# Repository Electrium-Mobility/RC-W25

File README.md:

# RC-W25
Electrium Mobility W25 Remote Control Project

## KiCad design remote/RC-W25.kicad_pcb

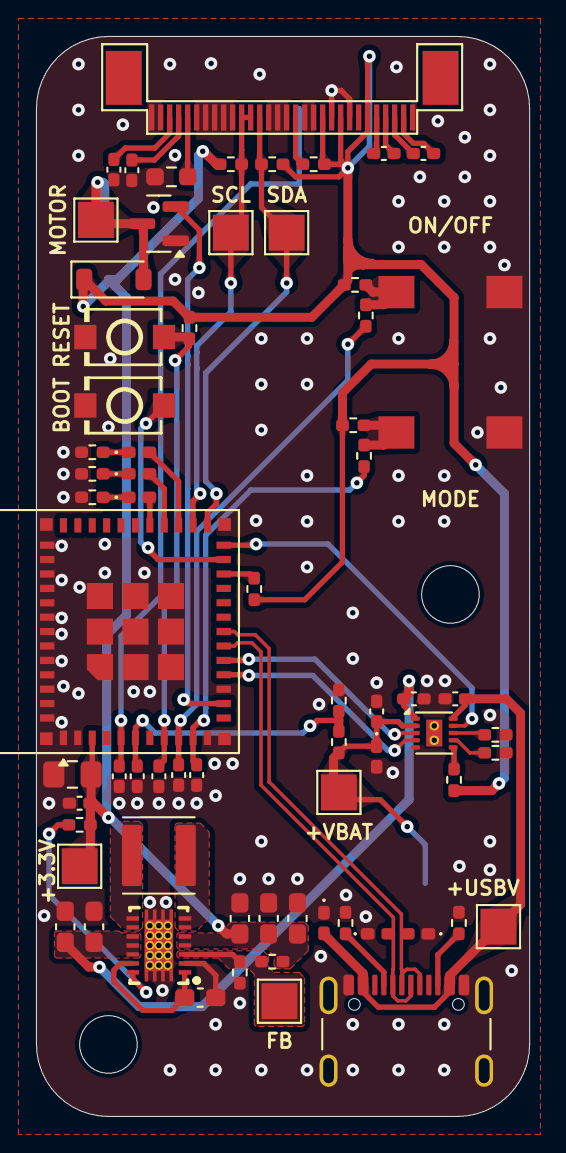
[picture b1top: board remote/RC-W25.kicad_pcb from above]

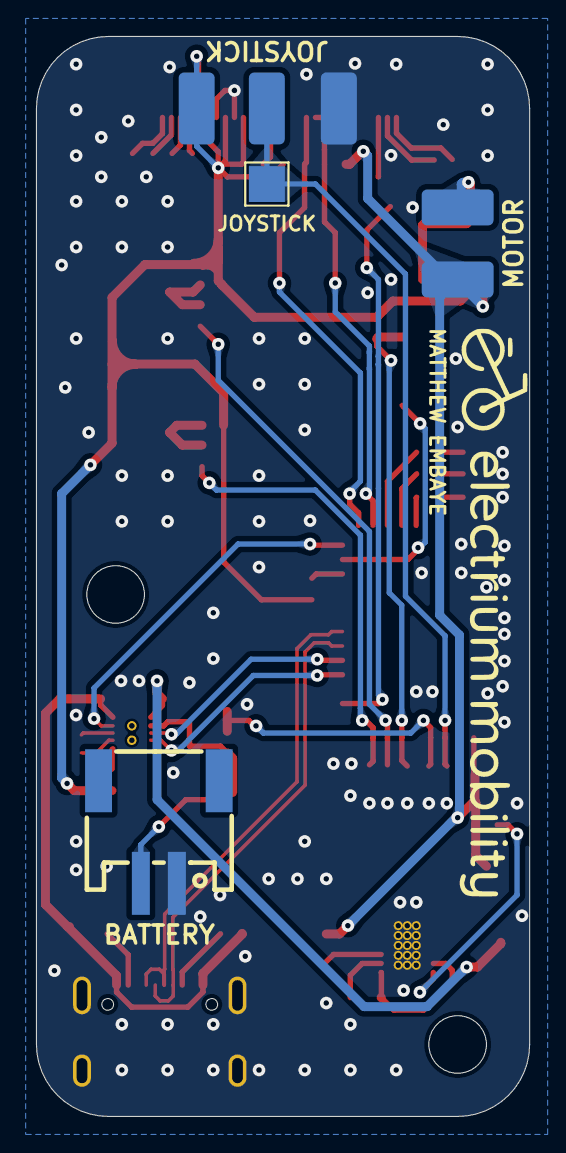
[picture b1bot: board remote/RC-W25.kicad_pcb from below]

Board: 2 copper layers, 27.4 x 60.0 mm, 75 parts (4 on the bottom side), 47 nets.

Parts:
+3.3V: TEST POINT; TestPoint_Pad_2.0x2.0mm
+USBV: TEST POINT; TestPoint_Pad_2.0x2.0mm
+VBAT: TEST POINT; TestPoint_Pad_2.0x2.0mm
BATTERY: JST CONN; CONN-SMD_2P-P2.00_XUNPU_WAFER-PH2.0-2PWB
BOOT: Button; SW-SMD_L3.9-W3.0-P4.45
C1, C10: 4.7uF; C_0402_1005Metric_Pad0.74x0.62mm_HandSolder
C2, C18: 10uF; C_0402_1005Metric_Pad0.74x0.62mm_HandSolder
C3, C4: 2.2uF; C_0402_1005Metric_Pad0.74x0.62mm_HandSolder
C5, C6, C7, C9, C19, C20: 100nF; C_0402_1005Metric_Pad0.74x0.62mm_HandSolder
C8: 22uF; C_0805_2012Metric_Pad1.18x1.45mm_HandSolder
C11, C12: 10uF; C_0603_1608Metric_Pad1.08x0.95mm_HandSolder
C13: 100nF; C_0603_1608Metric_Pad1.08x0.95mm_HandSolder
C14: 1uF; C_0402_1005Metric_Pad0.74x0.62mm_HandSolder
C15, C16, C17: 22uF; C_0603_1608Metric_Pad1.08x0.95mm_HandSolder
D1, D2, D3: 6V TVS; D_0402_1005Metric_Pad0.77x0.64mm_HandSolder
D4: RLED; D_0402_1005Metric_Pad0.77x0.64mm_HandSolder
D5: ORLED; D_0402_1005Metric_Pad0.77x0.64mm_HandSolder
D6: GLED; D_0402_1005Metric_Pad0.77x0.64mm_HandSolder
D7: ZENER 5V; D_0402_1005Metric_Pad0.77x0.64mm_HandSolder
D8: D_Schottky; D_SOD-123
DS1: FPC 30P; FPC-30P-0.5mm
FB: TEST POINT; TestPoint_Pad_2.0x2.0mm
H1, H2: MountingHole; MountingHole_3.2mm_M3
J1: USB_C_Receptacle_USB2.0_14P; USB_C_Receptacle_GCT_USB4105-xx-A_16P_TopMnt_Horizontal
JOYSTICK: TEST POINT; TestPoint_Pad_2.0x2.0mm
JOYSTICK#2: JOYSTICK; Joystick Potentiometer Pads
L1: 1.5uH; L_Abracon_ASPI-4030S
MODE: Button; Box Tactile Button Switch
MOTOR: TEST POINT; TestPoint_Pad_2.0x2.0mm
MOTOR#2: MOTOR; Motor Pads
ON/OFF: Button; Box Tactile Button Switch
Q1: NMOS; SOT-23
R1: 390k; R_0603_1608Metric_Pad0.98x0.95mm_HandSolder
R2, R3, R4: 4.7k; R_0402_1005Metric_Pad0.72x0.64mm_HandSolder
R5, R6: 5.1k; R_0402_1005Metric_Pad0.72x0.64mm_HandSolder
R7, R8, R20, R21, R22, R23: 10k; R_0402_1005Metric_Pad0.72x0.64mm_HandSolder
R9, R10, R11: 300; R_0402_1005Metric_Pad0.72x0.64mm_HandSolder
R12: 5k; R_0402_1005Metric_Pad0.72x0.64mm_HandSolder
R13, R14, R17: 1k; R_0402_1005Metric_Pad0.72x0.64mm_HandSolder
R15, R19: 1M; R_0402_1005Metric_Pad0.72x0.64mm_HandSolder
R16: 180k; R_0402_1005Metric_Pad0.72x0.64mm_HandSolder
R18: 3.7k; R_0402_1005Metric_Pad0.72x0.64mm_HandSolder
RESET: Button; SW-SMD_L3.9-W3.0-P4.45
SCL: TEST POINT; TestPoint_Pad_2.0x2.0mm
SDA: TEST POINT; TestPoint_Pad_2.0x2.0mm
U1: ESP32-C6-MINI-1
U2: BQ25185; WSON-10 BQ25185
U3: TPS63020; TPS63020_VSON(14)

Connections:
+3.3V: +3.3V.1, C8.1, C9.1, C15.1, C16.1, C17.1, D8.1 (K), DS1.6 (VPump), DS1.9 (VLogic), DS1.11 (BS1), JOYSTICK#2.1, MOTOR#2.2, R2.1, R3.1, R4.1, R7.1, R8.1, R14.1, R15.1, R19.1, R20.1, R21.1, U1.3 (3V3), U3.4 (VOUT), U3.5 (VOUT)
+USB5V: +USBV.1, C10.1, D2.2 (A2), J1.A4 (VBUS), J1.A9 (VBUS), J1.B4 (VBUS), J1.B9 (VBUS), U2.10 (IN)
+VBAT: +VBAT.1, BATTERY.2, C14.1, D7.1 (K), R17.1, U2.2 (BAT)
+VSYS: C11.1, C12.1, C18.1, U2.1 (SYS), U3.10 (VIN), U3.11 (VIN), U3.12 (EN)
/Connections/FLASH: BOOT.1, U1.23 (IO9)
/Connections/RESET: C7.1, R8.2, RESET.1, U1.8 (EN)
/Power/ILIM/VSET: R12.1, U2.7 (ILIM/VSET)
/Power/TS/MR: R14.2, U2.6 (TS/MR)
ADC_BATTERYPERCENT: C6.1, R17.2, R18.1, U1.6 (IO3)
ADC_JOYSTICK: C5.1, JOYSTICK.1, JOYSTICK#2.2, U1.5 (IO2)
CHSTAT1: U1.24 (IO18), U2.9 (STAT1)
CHSTAT2: U1.16 (IO7), U2.3 (STAT2)
CH_EN: U1.15 (IO6), U2.4 (CE)
GND: BATTERY.1, BOOT.2, C1.2, C2.2, C5.2, C6.2, C7.2, C8.2, C9.2, C10.2, C11.2, C12.2, C13.2, C14.2, C15.2, C16.2, C17.2, C18.2, C19.2, C20.2, D1.1 (A1), D2.1 (A1), D3.1 (A1), D7.2 (A), DS1.1 (GND), DS1.8 (GND), DS1.10 (BS0), DS1.12 (BS2), DS1.13 (C/S), DS1.15 (D/C), DS1.16 (R/W), DS1.17 (E/RD), DS1.21 (D3), DS1.22 (D4), DS1.23 (D5), DS1.24 (D6), DS1.25 (D7), DS1.29 (GND-A), DS1.30 (GND), J1.A1 (GND), J1.A12 (GND), J1.B1 (GND), J1.B12 (GND), J1.S1 (SHIELD), JOYSTICK#2.3, MODE.2, ON/OFF.2, Q1.1 (D), R1.2, R5.2, R6.2, R9.2, R10.2, R11.2, R12.2, R13.2, R16.2, R18.2, RESET.2, U1.1 (GND), U1.2 (GND), U1.11 (GND), U1.14 (GND), U1.36 (GND), U1.37 (GND), U1.38 (GND), U1.39 (GND), U1.40 (GND), U1.41 (GND), U1.42 (GND), U1.43 (GND), U1.44 (GND), U1.45 (GND), U1.46 (GND), U1.47 (GND), U1.48 (GND), U1.49 (GND), U1.50 (GND), U1.51 (GND), U1.52 (GND), U1.53 (GND), U2.5 (GND), U3.2 (GND), U3.15 (PGND)
GPIO_MODE: C19.1, R22.2, U1.10 (IO5)
GPIO_RUMBLE_CNTL: Q1.2 (G), U1.13 (IO1)
unnamed: D4.2 (A), U1.27 (IO21)
unnamed: D4.1 (K), R9.1
unnamed: D5.2 (A), U1.28 (IO22)
unnamed: D5.1 (K), R10.1
unnamed: D6.2 (A), U1.29 (IO23)
unnamed: D6.1 (K), R11.1
unnamed: D8.2 (A), MOTOR.1, MOTOR#2.1, Q1.3 (S)
unnamed: C4.2, DS1.5 (C1N)
unnamed: C4.1, DS1.4 (C1P)
unnamed: C3.2, DS1.3 (C2N)
unnamed: C3.1, DS1.2 (C2P)
unnamed: DS1.26 (IREF), R1.1
unnamed: DS1.14 (Reset), R3.2
unnamed: C1.1, DS1.27 (VCOMH)
unnamed: C2.1, DS1.28 (VDisplay)
unnamed: J1.A5 (CC1), R6.1
unnamed: J1.B5 (CC2), R5.1
unnamed: L1.1, U3.8 (L1), U3.9 (L1)
unnamed: L1.2, U3.6 (L2), U3.7 (L2)
unnamed: MODE.1, R20.2, R22.1
unnamed: ON/OFF.1, R21.2, R23.1
unnamed: R7.2, U1.22 (IO8)
unnamed: R13.1, U2.8 (ISET)
unnamed: FB.1, R15.2, R16.1, U3.3 (FB)
unnamed: R19.2, U3.14 (PG)
unnamed: C13.1, U3.1 (VINA), U3.13 (PS/SYNC)
ON/OFF: C20.1, R23.2, U1.9 (IO4)
SCL_DISPLAY: DS1.19 (D1), DS1.20 (D2), R4.2, SCL.1, U1.26 (IO20)
SDA_DISPLAY: DS1.18 (D0), R2.2, SDA.1, U1.25 (IO19)
USB_D+: D1.2 (A2), J1.A6 (D+), J1.B6 (D+), U1.18 (IO13)
USB_D-: D3.2 (A2), J1.A7 (D-), J1.B7 (D-), U1.17 (IO12)

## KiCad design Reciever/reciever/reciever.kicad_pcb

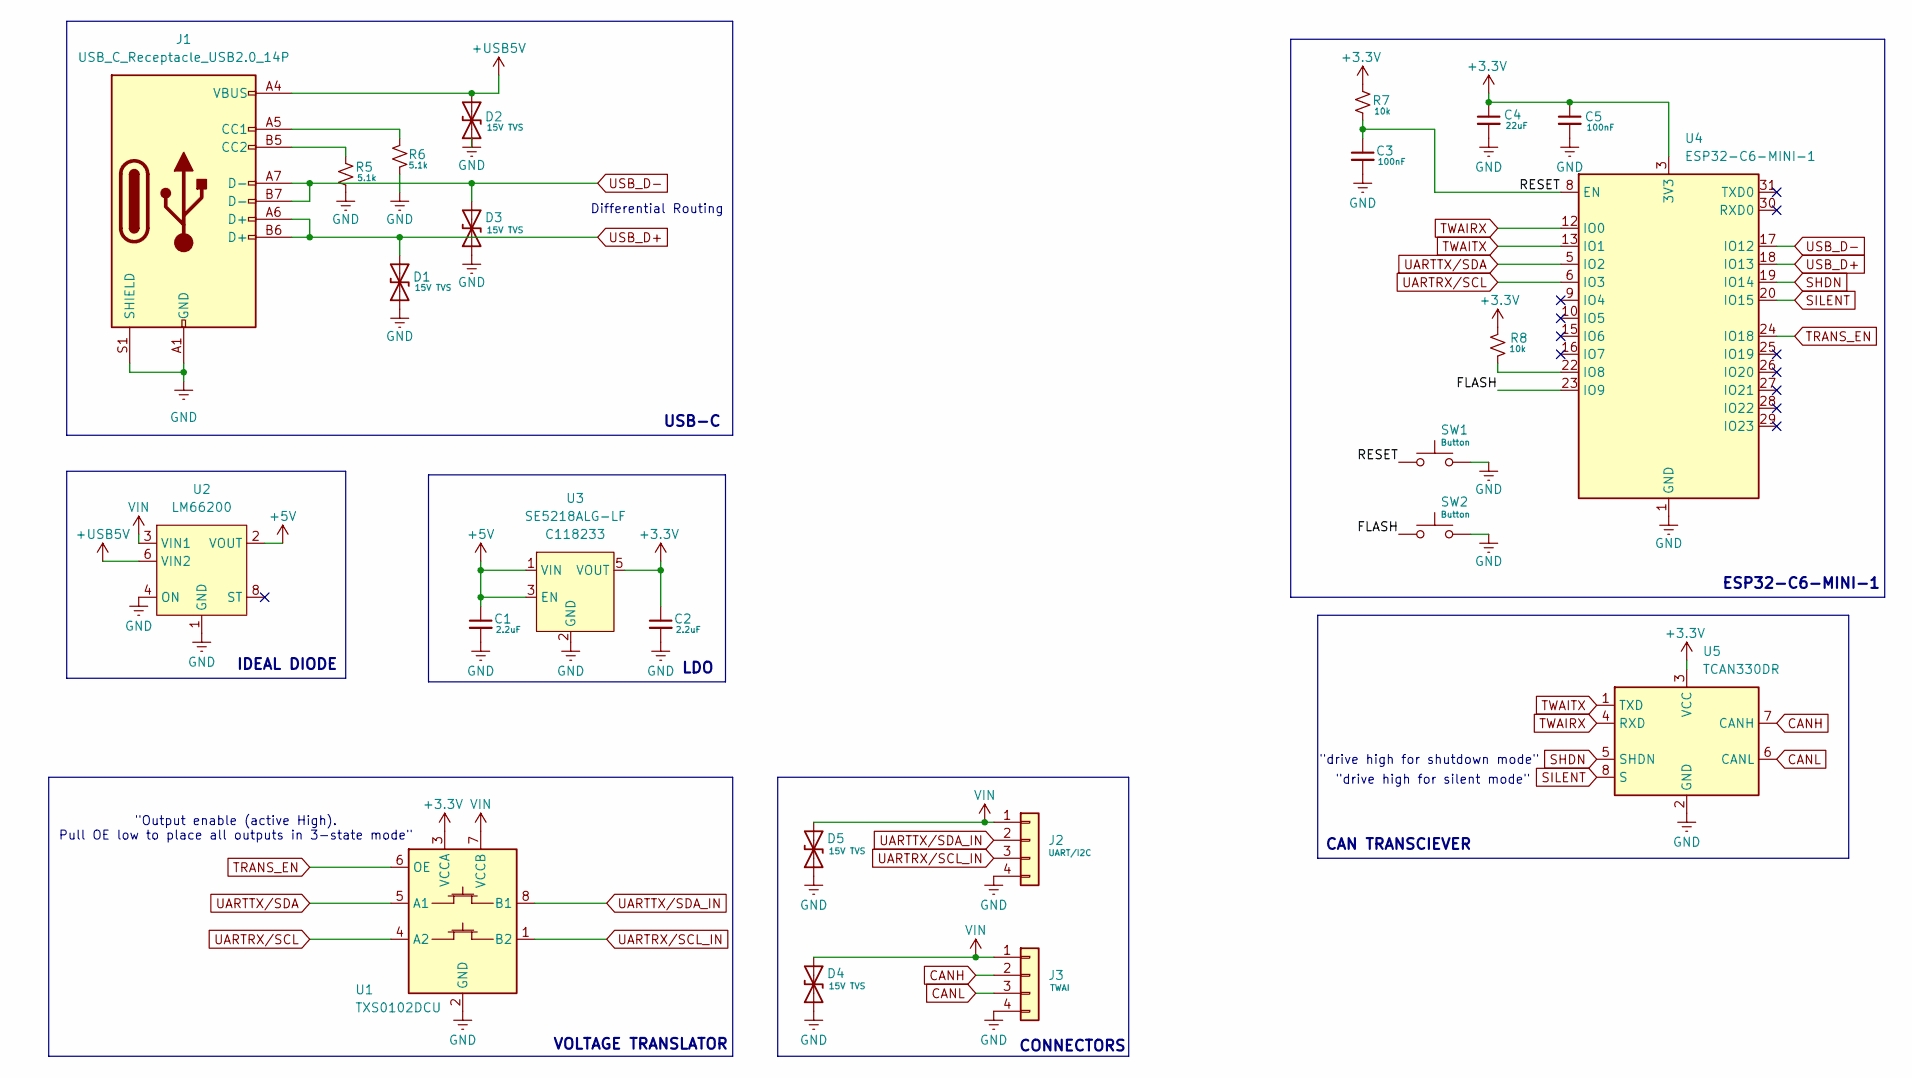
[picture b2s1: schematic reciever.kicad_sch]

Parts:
C1, C2: 2.2uF; C_0402_1005Metric; MPN C338067; LCSC# C338067
C3, C5: 100nF; C_0402_1005Metric; MPN C22435938; LCSC# C22435938
C4: 22uF; C_0805_2012Metric; MPN C380337; LCSC# C380337
D1, D2, D3, D4, D5: 15V TVS; D_0402_1005Metric; MPN C316043; LCSC# C316043
J1: USB_C_Receptacle_USB2.0_14P; USB_C_Receptacle_GCT_USB4105-xx-A_16P_TopMnt_Horizontal; MPN C165948; LCSC# C165948
J2: UART/I2C; CONN-SMD_PH2.0-4PWB; MPN C50137; LCSC# C50137
J3: TWAI; CONN-SMD_PH2.0-4PWB; MPN C50137; LCSC# C50137
R5, R6: 5.1k; R_0402_1005Metric; MPN C852861; LCSC# C852861
R7, R8: 10k; R_0402_1005Metric; MPN C190095; LCSC# C190095
SW1, SW2: Button; SW-SMD_L3.9-W3.0-P4.45; MPN C720477; LCSC# C720477
U1: TXS0102DCU; VSSOP-8_2.3x2mm_P0.5mm; MPN C53434; LCSC# C53434
U2: LM66200; SOT-583-8; MPN C3235556; LCSC# C3235556
U3: SE5218ALG-LF; SOT-23-5; MPN C118233; LCSC# C118233
U4: ESP32-C6-MINI-1; MPN C5736265; LCSC# C5736265
U5: TCAN330DR; SOIC-8-1EP_3.9x4.9mm_P1.27mm_EP2.29x3mm; MPN C2652876; LCSC# C2652876

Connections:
+3.3V: C2.1, C4.1, C5.1, R7.1, R8.1, U1.3 (VCCA), U3.5 (VOUT), U4.3 (3V3), U5.3 (VCC)
+5V: C1.1, U2.2 (VOUT), U2.7 (VOUT), U3.1 (VIN), U3.3 (EN)
+USB5V: D2.2 (A2), J1.A4 (VBUS), J1.A9 (VBUS), J1.B4 (VBUS), J1.B9 (VBUS), U2.6 (VIN2)
/FLASH: SW2.1, U4.23 (IO9); also elsewhere on the board
/RESET: C3.1, R7.2, SW1.1, U4.8 (EN); also elsewhere on the board
CANH: J3.2, U5.7 (CANH)
CANL: J3.3, U5.6 (CANL)
GND: C1.2, C2.2, C3.2, C4.2, C5.2, D1.1 (A1), D2.1 (A1), D3.1 (A1), D4.1 (A1), D5.1 (A1), J1.A1 (GND), J1.A12 (GND), J1.B1 (GND), J1.B12 (GND), J1.S1 (SHIELD), J2.4, J3.4, R5.2, R6.2, SW1.2, SW2.2, U1.2 (GND), U2.1 (GND), U2.4 (ON), U2.5 (GND), U3.2 (GND), U4.1 (GND), U4.2 (GND), U4.11 (GND), U4.14 (GND), U4.36 (GND), U4.37 (GND), U4.38 (GND), U4.39 (GND), U4.40 (GND), U4.41 (GND), U4.42 (GND), U4.43 (GND), U4.44 (GND), U4.45 (GND), U4.46 (GND), U4.47 (GND), U4.48 (GND), U4.49 (GND), U4.50 (GND), U4.51 (GND), U4.52 (GND), U4.53 (GND), U5.2 (GND); also elsewhere on the board
unnamed: J1.A5 (CC1), R6.1
unnamed: J1.B5 (CC2), R5.1
unnamed: R8.2, U4.22 (IO8)
SHDN: U4.19 (IO14), U5.5 (SHDN)
SILENT: U4.20 (IO15), U5.8 (S)
TRANS_EN: U1.6 (OE), U4.24 (IO18)
TWAIRX: U4.12 (IO0), U5.4 (RXD)
TWAITX: U4.13 (IO1), U5.1 (TXD)
UARTRX/SCL: U1.4 (A2), U4.6 (IO3)
UARTRX/SCL_IN: J2.3, U1.1 (B2)
UARTTX/SDA: U1.5 (A1), U4.5 (IO2)
UARTTX/SDA_IN: J2.2, U1.8 (B1)
USB_D+: D1.2 (A2), J1.A6 (D+), J1.B6 (D+), U4.18 (IO13)
USB_D-: D3.2 (A2), J1.A7 (D-), J1.B7 (D-), U4.17 (IO12)
VIN: D4.2 (A2), D5.2 (A2), J2.1, J3.1, U1.7 (VCCB), U2.3 (VIN1)

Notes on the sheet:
"drive high for silent mode"
"Output enable (active High). Pull OE low to place all outputs in 3-state mode"
USB-C
Differential Routing
VOLTAGE TRANSLATOR
CONNECTORS
"drive high for shutdown mode"
ESP32-C6-MINI-1
IDEAL DIODE
LDO
CAN TRANSCIEVER

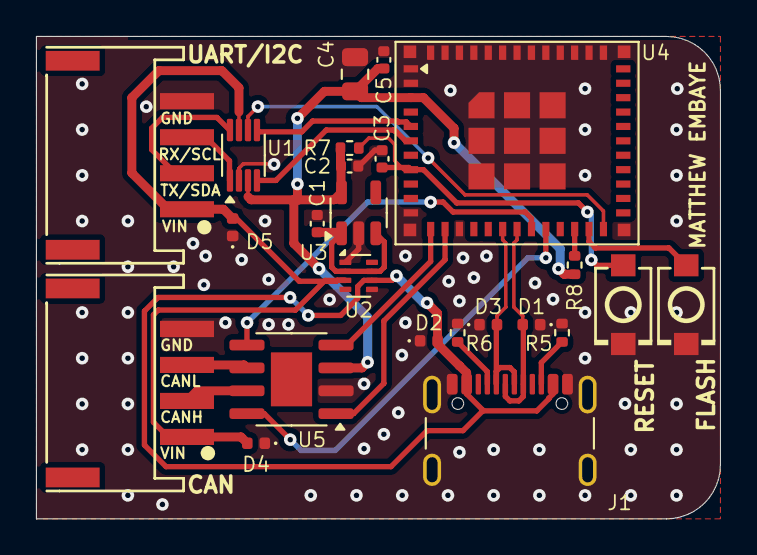
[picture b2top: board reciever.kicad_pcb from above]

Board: 2 copper layers, 38.0 x 26.8 mm, 24 parts (0 on the bottom side), 23 nets.

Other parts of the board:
FLASH: Button; SW-SMD_L3.9-W3.0-P4.45
RESET: Button; SW-SMD_L3.9-W3.0-P4.45

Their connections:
/FLASH: FLASH.1; also elsewhere on the board
/RESET: RESET.1; also elsewhere on the board
GND: FLASH.2, RESET.2; also elsewhere on the board

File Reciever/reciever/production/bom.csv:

Designator,Footprint,Quantity,Value,LCSC Part #
"C1, C2",0402,2,2.2uF,C338067
"C3, C5",0402,2,100nF,C22435938
C4,0805,1,22uF,C380337
"D1, D2, D3",0402,3,6V TVS,C316043
"D4, D5",D_SOD-123,2,D_Schottky,C41376455
J1,USB_C_Receptacle_GCT_USB4105-xx-A_16P_TopMnt_Horizontal,1,USB_C_Receptacle_USB2.0_14P,C165948
J2,CONN-SMD_PH2.0-4PWB,1,UART/I2C,C50137
J3,CONN-SMD_PH2.0-4PWB,1,TWAI,C50137
"R5, R6",0402,2,5.1k,C852861
"R7, R8",0402,2,10k,C190095
"SW1, SW2",SW-SMD_L3.9-W3.0-P4.45,2,Button,C720477
U1,VSSOP-8_2.3x2mm_P0.5mm,1,TXS0102DCU,C53434
U2,SOT-583-8,1,LM66200,C3235556
U3,SOT-23-5,1,SE5218ALG-LF,C118233
U4,ESP32-C6-MINI-1,1,ESP32-C6-MINI-1,C5736265
U5,SOIC-8-1EP_3.9x4.9mm_P1.27mm_EP2.29x3mm,1,TCAN330DR,C2652876

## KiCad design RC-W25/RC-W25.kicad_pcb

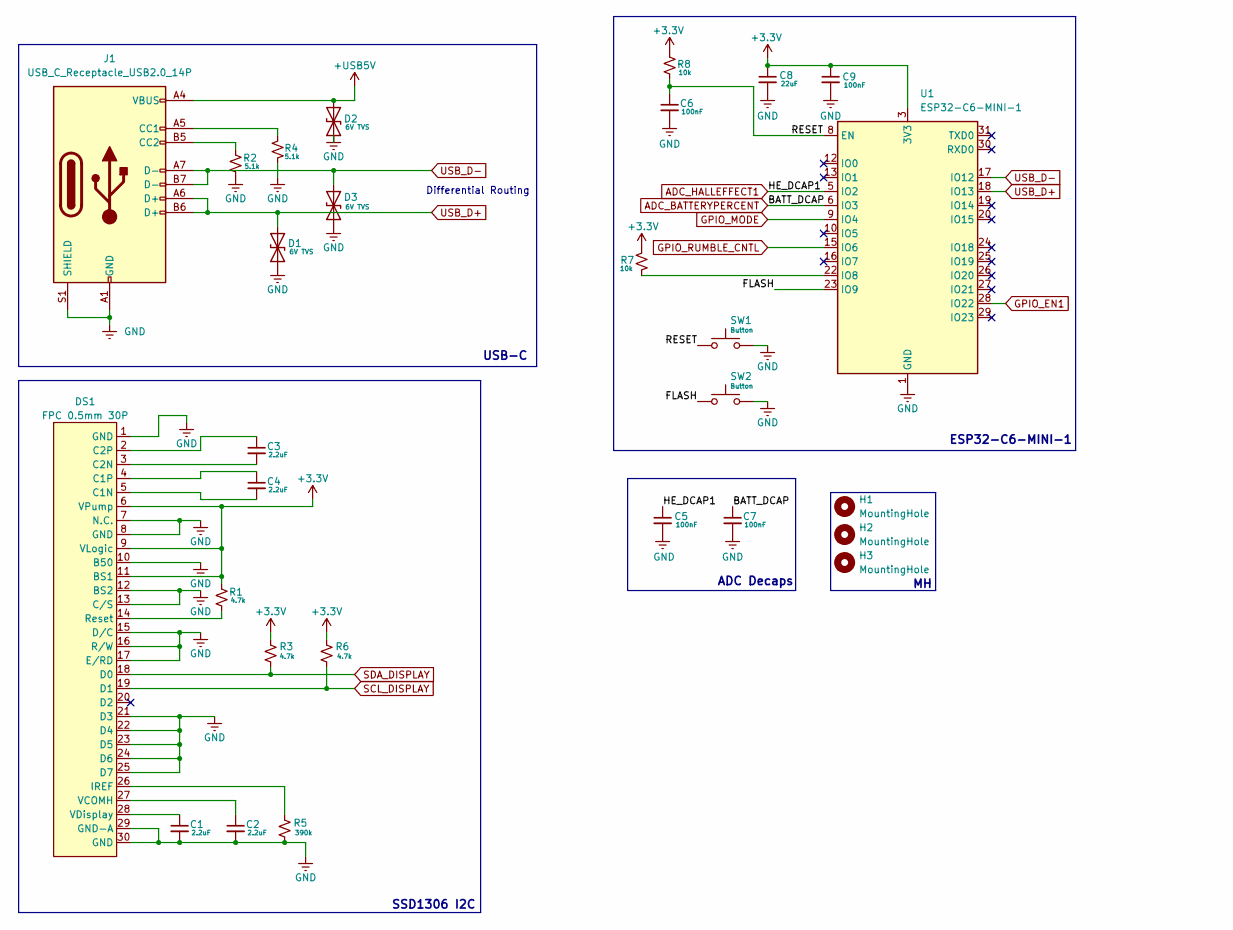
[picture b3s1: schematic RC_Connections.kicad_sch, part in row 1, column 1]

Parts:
C1, C2, C3, C4: 2.2uF; C_0402_1005Metric; MPN C12530; LCSC# C12530
C5, C6, C7, C9: 100nF; C_0402_1005Metric; MPN C1525; LCSC# C1525
C8: 22uF; C_0805_2012Metric; MPN C87997; LCSC# C87997
D1, D2, D3: 6V TVS; D_0402_1005Metric; MPN C316043; LCSC# C316043
DS1: FPC 0.5mm 30P; FPC-30P-0.5mm; MPN C2856808; LCSC# C2856808
H1, H2, H3: MountingHole; MountingHole_3.2mm_M3
J1: USB_C_Receptacle_USB2.0_14P; USB_C_Receptacle_GCT_USB4105-xx-A_16P_TopMnt_Horizontal; MPN C165948; LCSC# C165948
R1, R3, R6: 4.7k; R_0402_1005Metric; MPN C317921; LCSC# C317921
R2, R4: 5.1k; R_0402_1005Metric; MPN C490833; LCSC# C490833
R5: 390k; R_0603_1608Metric; MPN C861364; LCSC# C861364
R7, R8: 10k; R_0402_1005Metric; MPN C190095; LCSC# C190095
SW1, SW2: Button; SW-SMD_L3.9-W3.0-P4.45; MPN C720477; LCSC# C720477
U1: ESP32-C6-MINI-1; MPN C5736265; LCSC# C5736265

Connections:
+3.3V: C8.1, C9.1, DS1.6 (VPump), DS1.9 (VLogic), DS1.11 (BS1), R1.1, R3.1, R6.1, R7.1, R8.1, U1.3 (3V3); also elsewhere on the board
+USB5V: D2.2 (A2), J1.A4 (VBUS), J1.A9 (VBUS), J1.B4 (VBUS), J1.B9 (VBUS); also elsewhere on the board
/RC_Connections/FLASH: SW2.1, U1.23 (IO9)
/RC_Connections/RESET: C6.1, R8.2, SW1.1, U1.8 (EN)
ADC_BATTERYPERCENT: C7.1, U1.6 (IO3); also elsewhere on the board
ADC_HALLEFFECT1: C5.1, U1.5 (IO2); also elsewhere on the board
GND: C1.2, C2.2, C5.2, C6.2, C7.2, C8.2, C9.2, D1.1 (A1), D2.1 (A1), D3.1 (A1), DS1.1 (GND), DS1.7 (N.C.), DS1.8 (GND), DS1.10 (B50), DS1.12 (BS2), DS1.13 (C/S), DS1.15 (D/C), DS1.16 (R/W), DS1.17 (E/RD), DS1.21 (D3), DS1.22 (D4), DS1.23 (D5), DS1.24 (D6), DS1.25 (D7), DS1.29 (GND-A), DS1.30 (GND), J1.A1 (GND), J1.A12 (GND), J1.B1 (GND), J1.B12 (GND), J1.S1 (SHIELD), R2.2, R4.2, R5.2, SW1.2, SW2.2, U1.1 (GND), U1.2 (GND), U1.11 (GND), U1.14 (GND), U1.36 (GND), U1.37 (GND), U1.38 (GND), U1.39 (GND), U1.40 (GND), U1.41 (GND), U1.42 (GND), U1.43 (GND), U1.44 (GND), U1.45 (GND), U1.46 (GND), U1.47 (GND), U1.48 (GND), U1.49 (GND), U1.50 (GND), U1.51 (GND), U1.52 (GND), U1.53 (GND); also elsewhere on the board
GPIO_EN1: U1.28 (IO22); also elsewhere on the board
GPIO_MODE: U1.9 (IO4); also elsewhere on the board
GPIO_RUMBLE_CNTL: U1.15 (IO6); also elsewhere on the board
unnamed: C4.2, DS1.5 (C1N)
unnamed: C4.1, DS1.4 (C1P)
unnamed: C3.2, DS1.3 (C2N)
unnamed: C3.1, DS1.2 (C2P)
unnamed: DS1.26 (IREF), R5.1
unnamed: DS1.14 (Reset), R1.2
unnamed: C2.1, DS1.27 (VCOMH)
unnamed: C1.1, DS1.28 (VDisplay)
unnamed: J1.A5 (CC1), R4.1
unnamed: J1.B5 (CC2), R2.1
unnamed: R7.2, U1.22 (IO8)
SCL_DISPLAY: DS1.19 (D1), R6.2
SDA_DISPLAY: DS1.18 (D0), R3.2
USB_D+: D1.2 (A2), J1.A6 (D+), J1.B6 (D+), U1.18 (IO13)
USB_D-: D3.2 (A2), J1.A7 (D-), J1.B7 (D-), U1.17 (IO12)

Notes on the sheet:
USB-C
Differential Routing
ESP32-C6-MINI-1
ADC Decaps
SSD1306 I2C

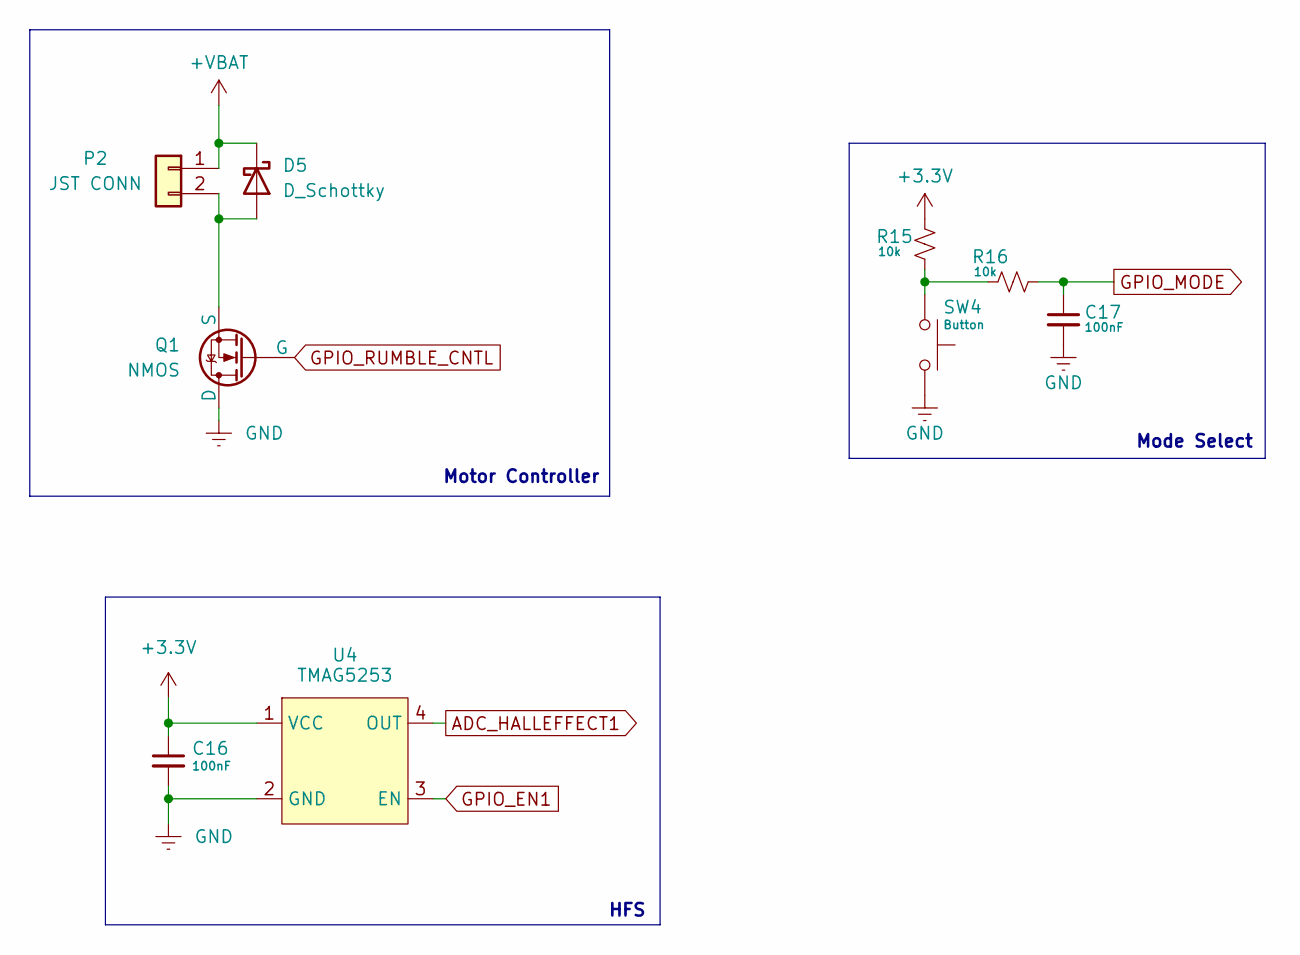
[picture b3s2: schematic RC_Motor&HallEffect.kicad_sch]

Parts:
C16, C17: 100nF; C_0402_1005Metric; MPN C1525; LCSC# C1525
D5: D_Schottky; D_SOD-123; MPN C64885; LCSC# C64885
P2: JST CONN; CONN-SMD_2P-P2.00_XUNPU_WAFER-PH2.0-2PWB; MPN C3029440; LCSC# C3029440
Q1: NMOS; SOT-23; MPN C443825; LCSC# C443825
R15, R16: 10k; R_0402_1005Metric; MPN C190095; LCSC# C190095
SW4: Button; SW-SMD_L3.9-W3.0-P4.45; MPN C720477; LCSC# C720477
U4: TMAG5253; X2SON4_DMR_TEX; MPN C22445458; LCSC# C22445458

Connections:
+3.3V: C16.1, R15.1, U4.1 (VCC); also elsewhere on the board
+VBAT: D5.1 (K), P2.1; also elsewhere on the board
ADC_HALLEFFECT1: U4.4 (OUT); also elsewhere on the board
GND: C16.2, C17.2, Q1.1 (D), SW4.2, U4.2 (GND); also elsewhere on the board
GPIO_EN1: U4.3 (EN); also elsewhere on the board
GPIO_MODE: C17.1, R16.2; also elsewhere on the board
GPIO_RUMBLE_CNTL: Q1.2 (G); also elsewhere on the board
unnamed: D5.2 (A), P2.2, Q1.3 (S)
unnamed: R15.2, R16.1, SW4.1

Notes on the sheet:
HFS
Motor Controller
Mode Select

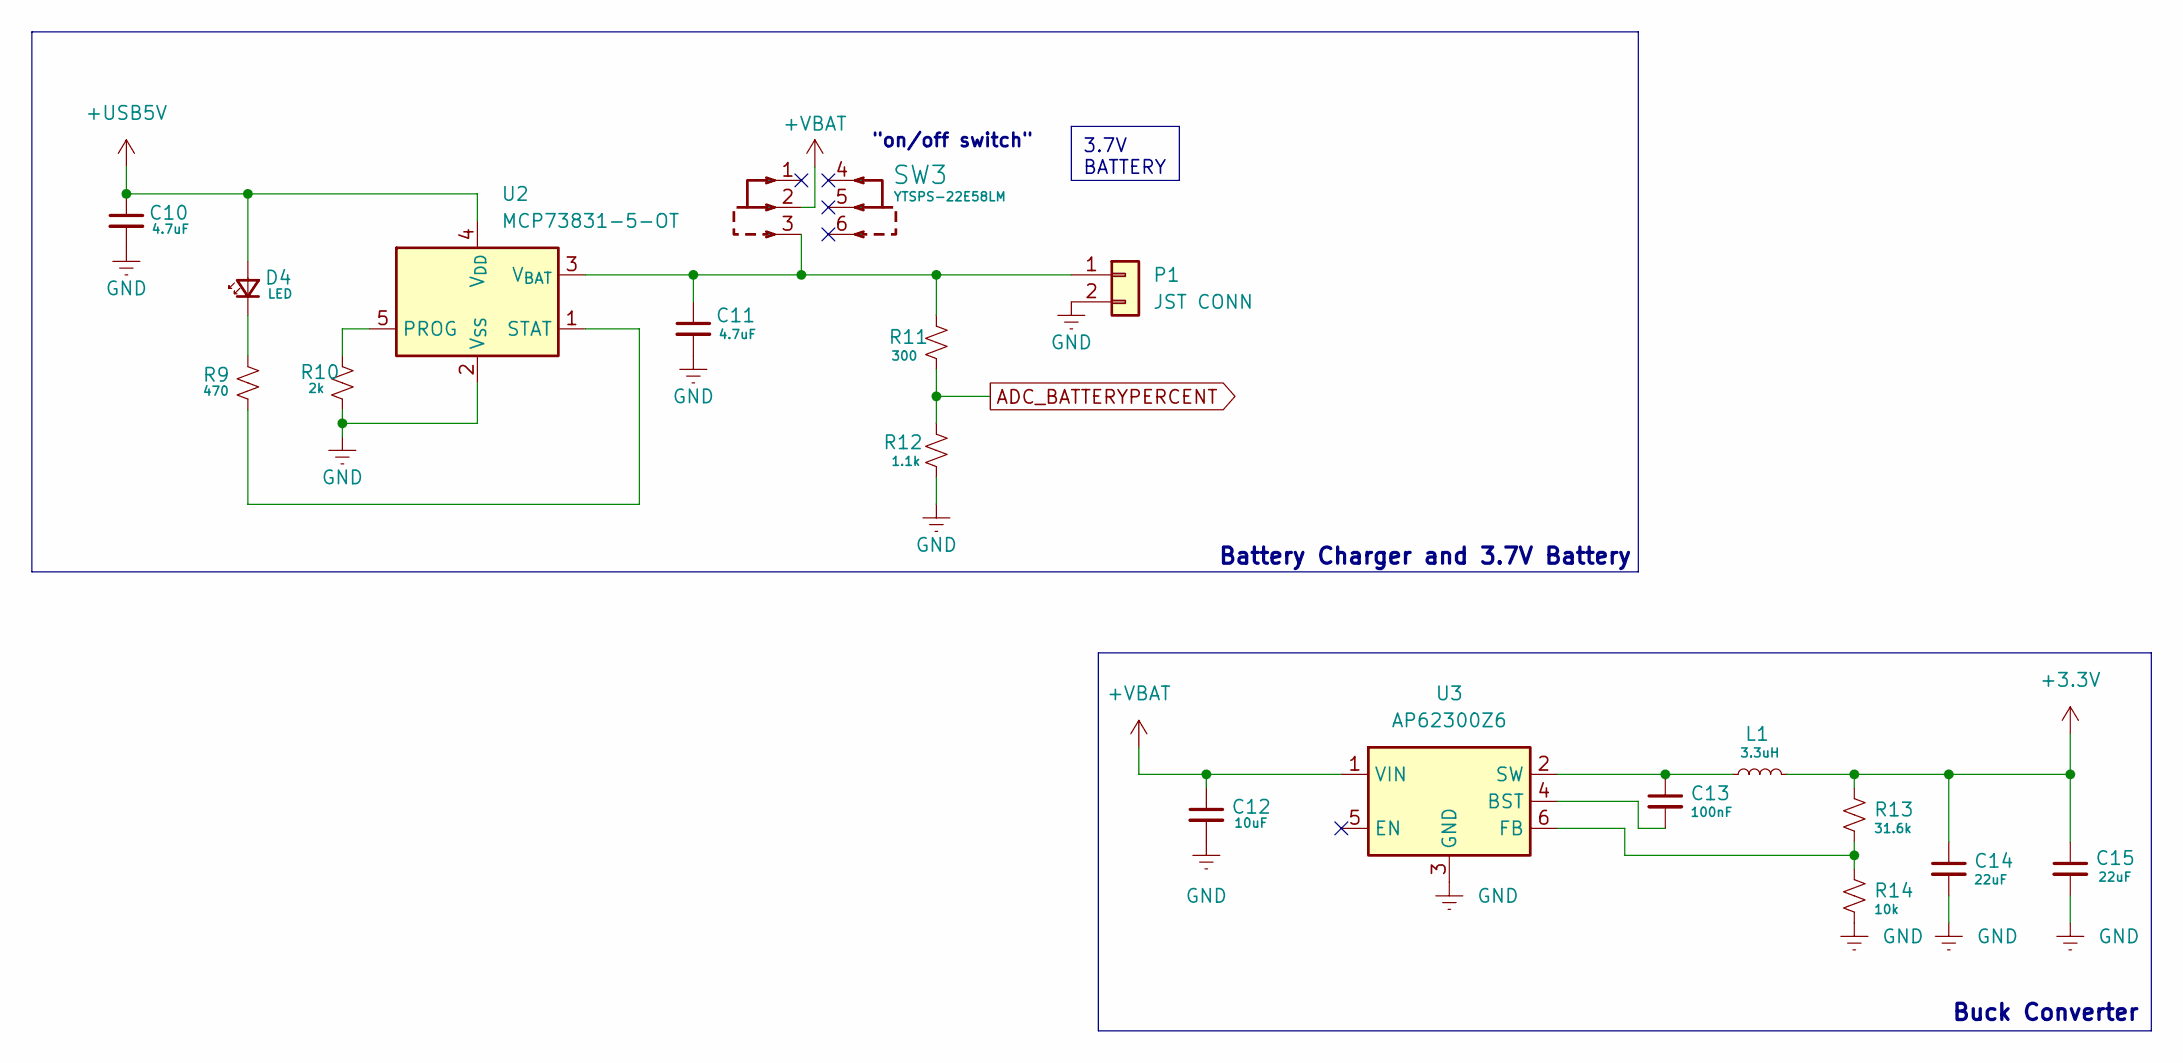
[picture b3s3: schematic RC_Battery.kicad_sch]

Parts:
C10, C11: 4.7uF; C_0402_1005Metric; MPN C23733; LCSC# C23733
C12: 10uF; C_0603_1608Metric; MPN C95839; LCSC# C95839
C13: 100nF; C_0402_1005Metric; MPN C1525; LCSC# C1525
C14, C15: 22uF; C_0805_2012Metric; MPN C87997; LCSC# C87997
D4: LED; D_0402_1005Metric; MPN C131223; LCSC# C131223
L1: 3.3uH; L_Abracon_ASPI-4030S; MPN C2050508; LCSC# C15269
P1: JST CONN; CONN-SMD_2P-P2.00_XUNPU_WAFER-PH2.0-2PWB; MPN C3029440; LCSC# C3029440
R9: 470; R_0402_1005Metric; MPN C852799; LCSC# C852799
R10: 2k; R_0402_1005Metric; MPN C2902640; LCSC# C2902640
R11: 300; R_0402_1005Metric; MPN C852712; LCSC# C852712
R12: 1.1k; R_0402_1005Metric; MPN C445597; LCSC# C445597
R13: 31.6k; R_0402_1005Metric; MPN C782222; LCSC# C782222
R14: 10k; R_0402_1005Metric; MPN C190095; LCSC# C190095
SW3: YTSPS-22E58LM; SW-SMD_6P-YTSPS-22E58LM; MPN C2941005; LCSC# C2941005
U2: MCP73831-5-OT; DFN-8-1EP_2x3mm_P0.5mm_EP0.61x2.2mm; MPN C635037; LCSC# C635037
U3: AP62300Z6; SOT-563; MPN C5250745

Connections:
+3.3V: C14.1, C15.1, L1.2, R13.1; also elsewhere on the board
+USB5V: C10.1, D4.2 (A), U2.4 (V_{DD}); also elsewhere on the board
+VBAT: C12.1, SW3.2, U3.1 (VIN); also elsewhere on the board
ADC_BATTERYPERCENT: R11.2, R12.1; also elsewhere on the board
GND: C10.2, C11.2, C12.2, C14.2, C15.2, P1.2, R10.2, R12.2, R14.2, U2.2 (V_{SS}), U3.3 (GND); also elsewhere on the board
unnamed: D4.1 (K), R9.1
unnamed: C11.1, P1.1, R11.1, SW3.3, U2.3 (V_{BAT})
unnamed: R10.1, U2.5 (PROG)
unnamed: R9.2, U2.1 (STAT)
unnamed: C13.2, U3.4 (BST)
unnamed: R13.2, R14.1, U3.6 (FB)
unnamed: C13.1, L1.1, U3.2 (SW)

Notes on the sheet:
3.7V BATTERY
{dblquote}on/off switch{dblquote}
Buck Converter
Battery Charger and 3.7V Battery

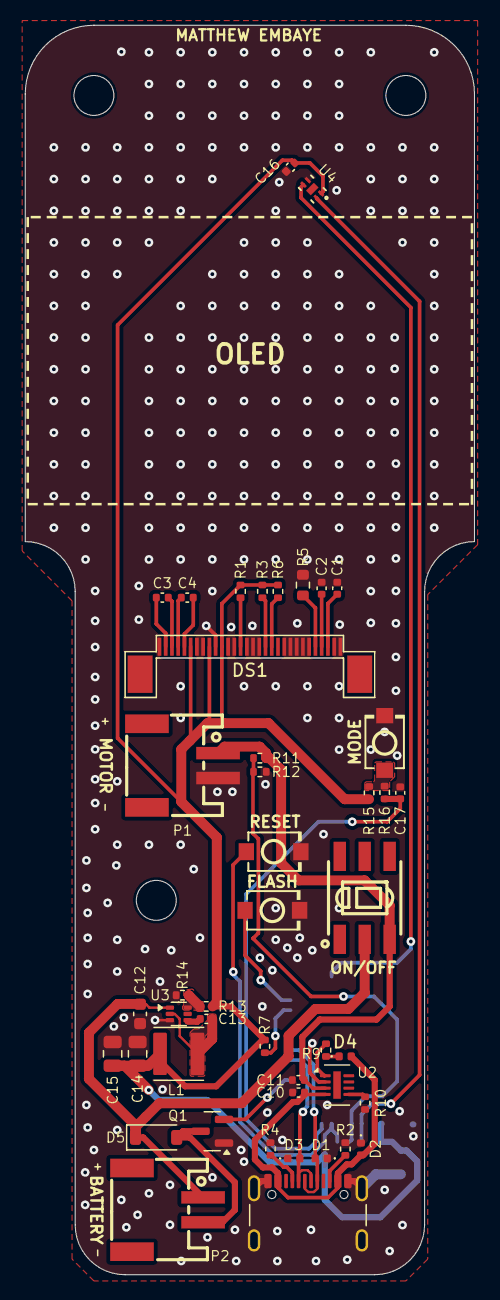
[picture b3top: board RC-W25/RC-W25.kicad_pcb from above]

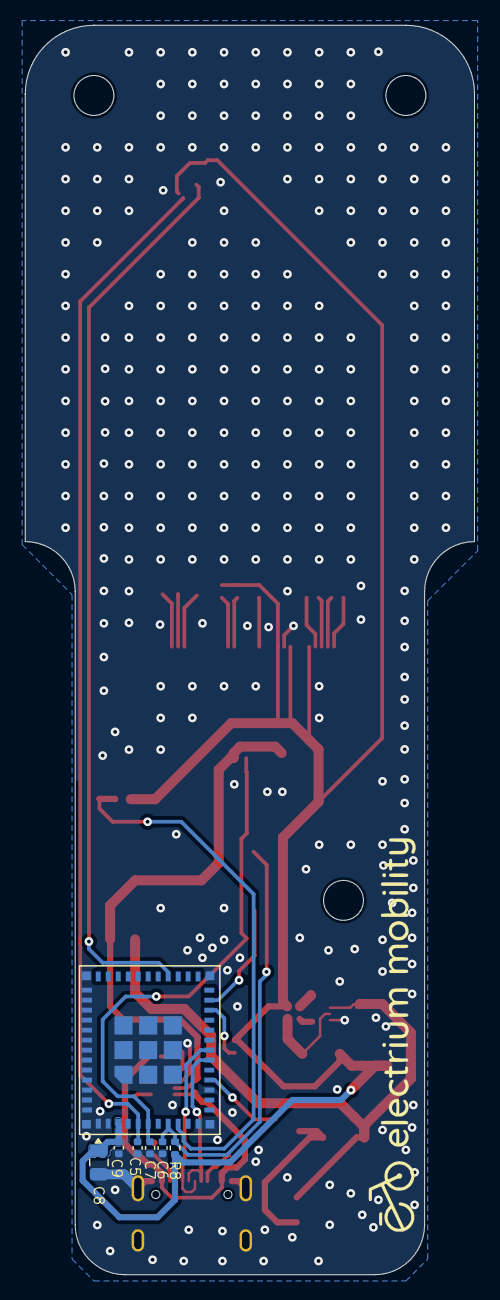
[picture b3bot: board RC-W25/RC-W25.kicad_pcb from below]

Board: 2 copper layers, 36.0 x 100.1 mm, 55 parts (7 on the bottom side), 35 nets.

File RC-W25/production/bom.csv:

Designator,Footprint,Quantity,Value,LCSC Part #
"C1, C2, C3, C4",0402,4,2.2uF,C12530
"C10, C11",0402,2,4.7uF,C23733
C12,0603,1,10uF,C95839
"C13, C16, C17, C5, C6, C7, C9",0402,7,100nF,C1525
"C14, C15, C8",0805,3,22uF,C87997
"D1, D2, D3",0402,3,6V TVS,C316043
D4,0402,1,LED,C131223
D5,D_SOD-123,1,D_Schottky,C64885
DS1,FPC-30P-0.5mm,1,FPC 0.5mm 30P,C2856808
J1,USB_C_Receptacle_GCT_USB4105-xx-A_16P_TopMnt_Horizontal,1,USB_C_Receptacle_USB2.0_14P,C165948
L1,L_Abracon_ASPI-4030S,1,3.3uH,C2050508
"P1, P2",CONN-SMD_2P-P2.00_XUNPU_WAFER-PH2.0-2PWB,2,JST CONN,C3029440
Q1,SOT-23,1,NMOS,C443825
"R1, R3, R6",0402,3,4.7k,C317921
R10,0402,1,2k,C2902640
R11,0402,1,300,C852712
R12,0402,1,1.1k,C445597
R13,0402,1,31.6k,C782222
"R14, R15, R16, R7, R8",0402,5,10k,C190095
"R2, R4",0402,2,5.1k,C490833
R5,0603,1,390k,C861364
R9,0402,1,470,C852799
"SW1, SW2, SW4",SW-SMD_L3.9-W3.0-P4.45,3,Button,C720477
SW3,SW-SMD_6P-YTSPS-22E58LM,1,YTSPS-22E58LM,C2941005
U1,ESP32-C6-MINI-1,1,ESP32-C6-MINI-1,C5736265
U2,DFN-8-1EP_2x3mm_P0.5mm_EP0.61x2.2mm,1,MCP73831-5-OT,C635037
U3,SOT-563,1,AP62300Z6,C5250745
U4,X2SON4_DMR_TEX,1,TMAG5253,C22445458

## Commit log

2025-01-28 Added fw directory
2025-01-28 Schematic Update
    Completed connections schematic
2025-01-28 Schematic Update
    Added buttons with debouncing and DC motor duraclik connector
2025-01-28 Updated Schematic
    Introduced linear hall effect sensors
2025-01-28 Configured platformio for esp32-c6
2025-02-05 Updated Battery
2025-02-06 fixed resistors
2025-02-07 updated main to continously read rumble control
2025-02-07 Updated Footprints
2025-02-07 ESP32 pairing with ESP-NOW
2025-02-07 Almost Finalized Schematic
    Still need to spec out buttons and jst conn
2025-02-08 ESP32 pairing file fix
2025-02-08 Created speed control file and header
    Includes hall effect, mode control and rumble control
2025-02-09 Began Routing
    Only need to spec out buttons before completion
2025-02-10 EM Custom RC V1
2025-02-10 em crc v1
    remaining tasks:
    - clean up + verify
    - potentially try to lose the 3 via jumps
    - spec out jst connectors
2025-02-10 crc v1
    finalized!! finally!! yes!!
    - spec out 3.7V 1000mAh cell
    - spec out ultra-thin coin motor
    ^make sure they have a jst-ph male connector or are organized to be ordered alongside one for manual soldering.
2025-02-11 ESP NOW works, split into .h and .c files
2025-02-11 Updated speed control with magnitude and direction functions
2025-02-11 Updated speed_control.c
2025-02-12 crc v1
    board complete and ready for assembly setup!
2025-02-12 crc v1
    board complete and ready for assembly setup
2025-02-12 crc v1
    board finished and ready for assembly setup!
2025-02-12 crc v1
    quick fixes
2025-02-12 crc v2
    finalizing receiver layout
2025-02-13 crc v2
    main board and receiver finalized. ready for assembly!
2025-02-14 crc v2
    remote and receiver complete! assembly and orders have been prepared for purchasing.
2025-02-18 Sorted out hall effect readings and made them more robust
2025-02-18 Added Deep Sleep and 3 Minute Inactivity Timer
2025-02-19 Custom RC V2
    Final Remote + Receiver!
    Special thanks to the CRCW25 Electrical Team who contributed to its development!
    Jun
    Katie
    Nelson
    David
2025-02-19 Added init file and changed deep sleep to light sleep
2025-02-19 light sleep uses ADC pin to wake up now
2025-02-24 Modified throttle readings to use 1 hall sensor
2025-02-24 Added global variables to pairing struct and implemented safe mode
2025-02-24 small changes so it compiles
2025-02-24 Added SSD1306 driver and set up display boilerplate
2025-02-24 Merged firmware updates into main
2025-02-24 displaying board battery percentage done
2025-02-26 driver was being goofy, added battery icon
2025-02-27 Added display
2025-02-27 Electrium logo on boot
2025-02-27 Configured I2C display pins and added mutexes for esp now
2025-02-27 displays speed
2025-02-28 compiles now
2025-03-03 warning message when board is off
2025-03-03 Initialized receiver, still need to set up vescUart library for esp idf and not arduino
2025-03-05 Set up Vesc uart library and ported it to esp idf (i think)
2025-03-05 fixed vescuart library and uart pin assignments
2025-03-06 determine_speed() function created
2025-03-06 Added direction to pairing struct, now accessible within receiver
2025-03-07 Apply throttle to ESC via UART
2025-03-07 Updated vesc_comm.c with battery percentage calculation
2025-03-13 added casing repo
2025-03-18 Debounced safemode button
2025-03-24 Added rumble patterns
2025-03-24 Small changes
2025-03-26 updated traces
2025-04-02 Updated pin assignments and implemented charging LEDs
2025-04-03 Added on off deep sleep functionality
2025-04-03 Updated throttle
2025-04-03 CRC V3
    V 3.0.0
    Initial version of CRC V3, fully redesigned remote
2025-04-03 Modified on off button to use an ISR
2025-04-14 basic RTOS scheduling for receiver and it compiles now
2025-04-15 Updated debouncing
2025-04-17 RCW25
    Finalized for order
2025-04-17 Small changes after testing, display and latency are pretty scuffed
2025-04-17 Fixed latency issues display may still be kinda scuffed
2025-04-17 Added safe mode ISR
2025-04-18 Finalized design for review and order
2025-04-19 Smoothened wheel and light sleep works, deep sleep almost works
2025-04-21 Fixed display rerendering and display watchdog blocking watchdog issue
2025-04-21 Deep sleep interrupt now works and added safe mode to display
2025-04-21 Changed direction logic to just be 1 or -1 to reduce transmission bandwidth
2025-04-21 Split pairing into two structs so we don't send redundant info either way
2025-04-21 Clear screen in deep sleep
2025-04-22 Fixed warning rerendering and CAN forwarding and added logo when turning off
2025-04-23 MAC address for actual receiver
2025-04-23 Uses UART connector instead of CAN connector pins now
2025-04-24 Logs show now and ESP NOW works on receiver side but UART doesn't
